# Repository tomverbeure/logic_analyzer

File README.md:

# logic_analyzer

* [Agilent - Probing Solutions for Logic Analyzers](https://xdevs.com/doc/HP_Agilent_Keysight/agilentprobing.pdf)

    * HP/Agilent 01650-61608 - Sixteen-channel probe lead set
        * Also known as E5383A
        * 40 pins: 16 data input, 1 clk input, 2 +5V, 1 DNC, 18 signal ground, 2 +5V ground
        * RC network: 90k ohm/8.2pF
        * Need board connector that is 0.425" tall
    * [3M 8540-4500PL board connector](https://www.digikey.com/en/products/detail/3m/8540-4500PL/1306252)

* [Bidirectional TVS diode for protecting dual-rail power](https://electronics.stackexchange.com/questions/653141/bidirectional-tvs-diode-for-protecting-dual-rail-power)

# Cyclone II LVDS

* [AN 479: Design Guidelines for Implementing LVDS Interfaces in Cyclone Series Devices](https://www.google.com/url?sa=t&rct=j&q=&esrc=s&source=web&cd=&ved=2ahUKEwi85qzynZn9AhXWIkQIHaqIBsoQFnoECDIQAQ&url=https%3A%2F%2Fcdrdv2-public.intel.com%2F653866%2Fan479.pdf)

* [Cyclone® II Device Handbook, Volume 1, Chapter 11: High-Speed Differential Interfaces in Cyclone II Devices](https://www.intel.com/content/www/us/en/content-details/655206/cyclone-ii-device-handbook-volume-1-chapter-11-high-speed-differential-interfaces-in-cyclone-ii-devices.html)

    * RX max 805 Mbps, TX max 640 Mbps.
    * No Vref needed
    * 100 Ohm termination resistor at RX input buffer.
    * (De)serialization is done in core logic.
    * Page 5-63: LVDS receiver timing specification
    * Page 10-27: Pad Placement and DC Guidelines
        * single-ended input no closer than 4 pads away from LVDS I/O
        * single-ended output no closer than 5 pads away from LVDS I/O
        * Maximum 4 155MHz+ LVDS output channels per VCCIO and ground pair
        * Maximum 3 311MHz+ LVDS output channels per VCCIO and ground pair
        * LVDS outputs are 5 or more pads away from LVDS input pad

* [ALTLVDS_TX](https://www.intel.com/content/www/us/en/docs/programmable/683062/17-1/parameter-settings-22420.html)

* [Intel Pin List](https://www.intel.com/content/www/us/en/support/programmable/support-resources/devices/lit-dp.html)

* [LVDS PCB design guidelines](https://madpcb.com/glossary/lvds/)

* [TI - SNx5LVDSxx High-Speed Differential Line Drivers](https://www.ti.com/lit/ds/symlink/sn65lvds31.pdf)

    This datasheet is great for practical layout guidelines. See section 12.

* [TI - LVDS Design Notes](https://www.ti.com/lit/an/slla014a/slla014a.pdf)

    More design guidelines...

* [TI - LVDS Owner’s Manual](https://www.ti.com/lit/ug/snla187/snla187.pdf)

* [LMH7220 - High Speed Comparator with LVDS Outpu](https://www.ti.com/lit/ds/symlink/lmh7322.pdf)

    ~$6 a piece.

* [MAX40025CAWT+T - 280ps High-Speed Comparator, Ultra-Low Dispersion with LVDS Outputs](https://www.mouser.com/datasheet/2/609/MAX40025A_MAX40026-3128703.pdf)

    ~$4.4 a piece for 25+.

# Soldering

* Individual soldering tips on Aliexpress: https://www.aliexpress.us/item/3256802408178790.html
* Drag soldering: https://www.youtube.com/watch?v=5uiroWBkdFY 
* Soldering tips: 
    * Fat/round tip: TS-C4 - reballing
    * Ultra-fin tip: TS-I - fine SMD soldering/fixes
* Mini hotplate
    * https://hackspace.raspberrypi.com/articles/review-miniware-mhp30-mini-hot-plate-preheater
    * 
* BGA Reballing: https://www.youtube.com/watch?v=u8QLlpkyCpc
    * Uses a different jig that doesn't require screws: https://www.aliexpress.us/item/2251832660851140.html
        * magnets
        * rotating knob

* Direct heat reballing (using my jig): https://youtu.be/VTAU647jzzk?t=598
* EP2C35 on AliExpress: https://www.aliexpress.us/item/3256804913471850.html
* 3-in-1 desoldering station: https://www.aliexpress.us/item/3256803049300994.html

# Impedance

* [JLCPCB impedance calculator](https://cart.jlcpcb.com/impedanceCalculation)

    * Impedance + trace space
    * Impedance value: 100 Ohm
    * 4-layer
    * thickness: 1.6mm
    * outer layer (micro-strip)
    * impedance type: differential
    * trace space: 4 mil
    * Result: 
        * JLC3313: 3.49mil  <- chosen
        * JLC7628: 4.96mil
    * Controled impedance PCBs: https://jlcpcb.com/impedance
        * JLC3313
            * Prereg dielectric constant: 4.05
            * Solder mask dielectric constant: 3.8
            * Solder maks thickness: 0.8mil
    
# JLCPCB Plugin

* [Bouni/kicad-jlcpcb-tools](https://github.com/Bouni/kicad-jlcpcb-tools)
* Basic LCSC chips:
    * ESD: SRV05-4-P-T7
    * Voltage inverter: [ICL7660AIBAZA-T](https://www.lcsc.com/product-detail/DC-DC-Converters_RENESAS-ICL7660AIBAZA-T_C7881.html)

# Various

* [Schematic of RISC-V board that uses FT601Q](http://riskfive.com/RiskFive_devel_rev0_board_July_24_2018.pdf)

    * Uses the Xtal that I selected.
    * Uses 25MHz oscillator
    
* ESD info
    * [Littelfuse technical resources](https://www.littelfuse.com/products/tvs-diodes.aspx)
    * USB SS ESD: 
        * [Nexperia PUSB3AB4](https://www.digikey.com/en/products/detail/nexperia-usa-inc/PUSB3AB4Z/6575997)
        * [DigiKey search](https://www.digikey.com/en/products/filter/transient-voltage-suppressors-tvs/tvs-diodes/144?s=N4IgjCBcoKwGxyqAxlAZgQwDYGcCmANCAPZQDaIAnDAAyJFwAsYLlIRYjNNATO%2BGBowAHPxaMA7DX6NhMGM35Mw8Nhx4BmHmvCaN0jvsYaxG2jrAbKPCUubxRHCZVljntN9RMdZNsTBV6cHlNO0DbDiYJGDE4Z0dwCTBhb0T5BLAJYWiZOACNBJ5k7RAAXSIABwAXKBAAZSqAJwBLADsAcxAAXyIJOAhoEFRITFxCEnIQBBpKK34pGg0zMR4aYWEDEFkpCCJ5BUYlFhFY7JL1GE0I8C0aFVNVmmvLfok%2BQ1fN1Z44fX5vuB%2BJzMHjvRLMe5OX6UXaJCRcGJOeE0Q5EUFyJ7-NaXQrYniokBFNarf6MGEpUkwpJlSo1SD1JptTo9RJ-QbDUb4IikSAUWFg1IExFTeb8DIxcogaq1ACSrSqeHaeEa3Q4lGEbHZ6GwXImvJA0lKXWNQA)
    * [Low capacitance 1-channel bidirectional diode: PESD5V0H1BSNYL](https://www.digikey.com/en/products/detail/nexperia-usa-inc/PESD5V0H1BSNYL/12808361)

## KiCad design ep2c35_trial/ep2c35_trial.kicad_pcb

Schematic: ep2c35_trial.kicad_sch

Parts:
C1, C3, C31, C33, C35: 1n; C_0402_1005Metric
C2, C4, C9, C10, C11, C12, C13, C14, C15, C16, C17, C18, C21, C22, C32, C34, C36, C37, C38, C39, C40, C41, C42, C43, C44, C45, C46, C47, C48, C49, C50, C51, C52, C53, C54, C55, C56, C57, C58, C59, C60, C61, C62, C63, C64, C65, C66, C67, C68, C69, C70, C72: 100n; C_0402_1005Metric
C5, C6, C7: 0.1u; C_0402_1005Metric
C8: 4.7u; C_0402_1005Metric
C19, C20: 18p; C_0402_1005Metric
C23, C25: 2u; C_0805_2012Metric
C24, C26: 47u; C_1206_3216Metric
C27, C28, C29, C71, C73: 1u; C_0805_2012Metric
C30: 10u; C_0805_2012Metric
D1, D3, D4, D5, D6, D7, D8: LED; LED_0603_1608Metric
FB1, FB2, FB3: BLM18PG221SN1D; R_0603_1608Metric
J1, J2: Conn_02x21_Odd_Even; PinHeader_2x21_P1.27mm_Horizontal
J3: 3M_8540-4500PL
J4: USB3_B_Micro_Amphenol_GSB343K331HR; AMPHENOL_GSB343K331HR
J5: Conn_02x05_Odd_Even; PinHeader_2x05_P2.54mm_Vertical
J7, J11: Conn_01x03_Pin; PinHeader_1x03_P2.54mm_Vertical
J8, J9: Conn_01x02_Male; PinHeader_1x02_P2.54mm_Vertical
J10: Conn_02x10_Odd_Even; PinHeader_2x10_P1.27mm_Horizontal
R1: 1.6k/1%; R_0402_1005Metric
R2, R3, R4, R5, R6, R7, R10, R31, R32, R33, R34, R35, R36, R37, R38, R39, R40, R41, R42, R43, R44, R45, R46, R47, R48: 10k; R_0402_1005Metric
R8, R68, R69, R71: 5k; R_0402_1005Metric
R9, R72: 3k; R_0402_1005Metric
R11, R12, R13, R14, R15, R16, R17, R18, R19, R20, R21, R22, R23, R24, R25, R26, R27, R28, R29, R30: 100; R_0402_1005Metric
R49, R51, R52, R53, R54, R55, R70: 1k; R_0402_1005Metric
R56, R58, R59, R61, R62, R64, R65, R67: 120; R_0402_1005Metric
R57, R60, R63, R66: 170; R_0402_1005Metric
TP1: TestPoint; TestPoint_Pad_D1.0mm
U1: EP2C35F484; BGA-484_23.0x23.0mm_Layout22x22_P1.0mm
U2: MIC37302; S-PAK-5
U3: FT600Q-B-T; QFN-56-1EP_7x7mm_P0.4mm_FT600Q
U4: W25Q16JVSNIQ; SOIC-8_5.23x5.23mm_P1.27mm
U5: MIC39102; SOICN-8LD-PL-1
U6: MIC49150-1.2; SOICN-8LD-PL-1
U7: SP3003-02UTG; SOT-23-6
U8, U9, U10, U11, U17: SRV05-4; SOT-23-6
U12, U13: LM317_TO-252; TO-252-2
X1: FNETHE025; Oscillator_SMD_IQD_IQXO70-4Pin_7.5x5.0mm
Y1: ABM7-30.000MHZ-D2Y-T; Crystal_SMD_0603-2Pin_6.0x3.5mm_HandSoldering

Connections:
+1V0: C8.2, C16.2, C17.2, C18.2, U3.1 (AVDD), U3.23 (VD10), U3.26 (VD10), U3.31 (DV10), U3.37 (VD10), U3.50 (VD10)
+1V2: C3.1, C4.1, C37.1, C38.1, C39.1, C40.1, C41.1, C42.1, C43.1, C44.1, C45.1, C46.1, C47.1, C48.1, C49.1, D3.2 (A), J8.2, J9.1, U1.E5 (VCCD_PLL3), U1.F17 (VCCD_PLL2), U1.G8 (VCCINT), U1.G12 (VCCINT), U1.H8 (VCCINT), U1.H12 (VCCINT), U1.H13 (VCCINT), U1.J10 (VCCINT), U1.J11 (VCCINT), U1.J12 (VCCINT), U1.J13 (VCCINT), U1.K8 (VCCINT), U1.K9 (VCCINT), U1.K14 (VCCINT), U1.L9 (VCCINT), U1.L14 (VCCINT), U1.L16 (VCCINT), U1.M9 (VCCINT), U1.M14 (VCCINT), U1.N9 (VCCINT), U1.N14 (VCCINT), U1.P10 (VCCINT), U1.P11 (VCCINT), U1.P12 (VCCINT), U1.P13 (VCCINT), U1.P14 (VCCINT), U1.R10 (VCCINT), U1.R12 (VCCINT), U1.T12 (VCCINT), U1.T15 (VCCINT), U1.U6 (VCCD_PLL1), U1.U17 (VCCD_PLL4)
+1V2A: C1.1, C2.1, C30.2, C31.1, C32.1, C33.1, C34.1, C35.1, C36.1, FB3.2, U1.E6 (VCCA_PLL3), U1.F16 (VCCA_PLL2), U1.U7 (VCCA_PLL1), U1.U16 (VCCA_PLL4)
+2V5: C28.2, C50.1, C51.1, C52.1, C53.1, C54.1, C55.1, C56.1, C57.1, C58.1, C59.1, C69.1, D1.2 (A), J11.2, R5.1, R6.1, U1.AA1 (VCCIO1), U1.AA22 (VCCIO6), U1.AB2 (VCCIO8), U1.AB21 (VCCIO7), U1.M3 (VCCIO1), U1.M20 (VCCIO6), U1.P7 (VCCIO1), U1.P16 (VCCIO6), U1.T4 (VCCIO1), U1.T9 (VCCIO8), U1.T14 (VCCIO7), U1.T19 (VCCIO6), U1.V10 (VCCIO8), U1.V13 (VCCIO7), U1.W6 (VCCIO8), U1.W17 (VCCIO7), U1.Y11 (VCCIO8), U1.Y12 (VCCIO7), U6.3 (VIN)
+3.3V: C9.2, C10.2, C11.2, C12.2, C13.2, C14.2, C15.2, C21.1, C22.2, C25.2, C27.2, C60.1, C61.1, C62.1, C63.1, C64.1, C65.1, C66.1, C67.1, C68.1, C70.1, D8.2 (A), J5.4, J7.2, R2.1, R3.2, R4.2, R7.2, U1.A2 (VCCIO3), U1.A21 (VCCIO4), U1.B1 (VCCIO2), U1.B22 (VCCIO5), U1.C6 (VCCIO3), U1.C11 (VCCIO3), U1.C12 (VCCIO4), U1.D17 (VCCIO4), U1.E10 (VCCIO3), U1.E13 (VCCIO4), U1.G9 (VCCIO3), U1.G14 (VCCIO4), U1.G19 (VCCIO5), U1.J7 (VCCIO2), U1.J16 (VCCIO5), U1.L3 (VCCIO2), U1.L20 (VCCIO5), U3.15 (VCC33), U3.19 (VCC33), U3.22 (VDDA), U3.30 (VCC33), U3.38 (VCCIO), U3.44 (VCCIO), U3.52 (VCCIO), U4.8 (VCC), U5.1 (EN), U5.2 (IN), U6.1 (EN), U6.2 (VBIAS), U12.3 (VI), X1.4 (Vdd)
/1V2_LDO: C29.2, J8.1, U6.4 (VOUT)
/1V2_OPT: FB3.1, J9.2
/2V5_ADJ: R10.1, R31.2, U5.4 (ADJ)
/2V5_ADJ_LM: R68.1, R69.2, U12.1 (ADJ)
/2V5_LDO: C26.2, J11.1, R10.2, U5.3 (OUT)
/2V5_LM_LDO: C71.2, J11.3, R68.2, U12.2 (VO)
/3V3_ADJ: R8.1, R9.2, U2.5 (ADJ)
/3V3_ADJ_LM: R71.1, R72.2, U13.1 (ADJ)
/3V3_LDO: C24.2, J7.1, R8.2, U2.4 (VOUT)
/3V3_LM_LDO: C73.2, J7.3, R71.2, U13.2 (VO)
/CLK25: U1.A12 (CLK9/LVDSCLK4p/input), X1.3 (OUT)
/CONF_DONE: R6.2, U1.N18 (CONF_DONE)
/CRC_ERROR: TP1.1, U1.D3 (IO/CRC_ERROR/LVDS49p)
/DIG_CLK: R32.1, U1.L22 (CLK4/LVDSCLK2p/input)
/DIG_D0: R48.1, U1.C21 (IO/LVDS104n)
/DIG_D1: R47.1, U1.C22 (IO/LVDS104p)
/DIG_D2: R46.1, U1.D21 (IO/LVDS108n)
/DIG_D3: R45.1, U1.D22 (IO/LVDS108p)
/DIG_D4: R44.1, U1.E21 (IO/LVDS109n)
/DIG_D5: R43.1, U1.E22 (IO/LVDS109p)
/DIG_D6: R42.1, U1.F21 (IO/LVDS112n)
/DIG_D7: R41.1, U1.F22 (IO/LVDS112p)
/DIG_D8: R40.1, U1.G21 (IO/LVDS114n)
/DIG_D9: R39.1, U1.G22 (IO/LVDS114p)
/DIG_D10: R38.1, U1.H21 (IO/LVDS122n)
/DIG_D11: R37.1, U1.H22 (IO/LVDS122p)
/DIG_D12: R36.1, U1.J21 (IO/LVDS124n)
/DIG_D13: R35.1, U1.J22 (IO/LVDS124p)
/DIG_D14: R34.1, U1.K21 (IO/LVDS125n)
/DIG_D15: R33.1, U1.K22 (IO/LVDS125p)
/FT_BE0: U1.A8 (IO/LVDS62p), U3.2 (BE_0)
/FT_BE1: U1.B8 (IO/LVDS62n), U3.3 (BE_1)
/FT_CLK: U1.B3 (IO/DEV_CLRn/LVDS50n), U3.43 (CLK)
/FT_DATA0: U1.F2 (IO/LVDS36n), U3.33 (DATA_0)
/FT_DATA1: U1.E1 (IO/LVDS37p), U3.34 (DATA_1)
/FT_DATA2: U1.E2 (IO/LVDS37n), U3.35 (DATA_2)
/FT_DATA3: U1.D1 (IO/LVDS40p), U3.36 (DATA_3)
/FT_DATA4: U1.D2 (IO/LVDS40n), U3.39 (DATA_4)
/FT_DATA5: U1.C1 (IO/LVDS47p), U3.40 (DATA_5)
/FT_DATA6: U1.C2 (IO/LVDS47n), U3.41 (DATA_6)
/FT_DATA7: U1.A3 (IO/LVDS50p), U3.42 (DATA_7)
/FT_DATA8: U1.A4 (IO/LVDS51p), U3.45 (DATA_8)
/FT_DATA9: U1.B4 (IO/LVDS51n), U3.46 (DATA_9)
/FT_DATA10: U1.A5 (IO/LVDS52p), U3.47 (DATA_10)
/FT_DATA11: U1.B5 (IO/LVDS52n), U3.48 (DATA_11)
/FT_DATA12: U1.A6 (IO/LVDS53p), U3.53 (DATA_12)
/FT_DATA13: U1.B6 (IO/LVDS53n), U3.54 (DATA_13)
/FT_DATA14: U1.A7 (IO/LVDS61p), U3.55 (DATA_14)
/FT_DATA15: U1.B7 (IO/LVDS61n), U3.56 (DATA_15)
/FT_GPIO0: U1.D9 (IO/LVDS64p), U3.12 (GPIO0)
/FT_GPIO1: U1.C10 (IO/VREFB3N0), U3.13 (GPIO1)
/FT_OE_N: U1.A11 (IO/LVDS73p), U3.9 (OE_N)
/FT_RD_N: U1.B10 (IO/LVDS70n), U3.8 (RD_N)
/FT_RESET_N: U1.B11 (IO/LVDS73n), U3.10 (RESET_N)
/FT_RXF_N: U1.B9 (IO/LVDS67n), U3.5 (RXF_N)
/FT_SIWU_N: R7.1, U3.6 (SIWU_N)
/FT_TXE_N: U1.A9 (IO/LVDS67p), U3.4 (TXE_N)
/FT_WAKEUP_N: U1.C9 (IO/LVDS59p), U3.11 (WAKEUP_N)
/FT_WR_N: U1.A10 (IO/LVDS70p), U3.7 (WR_N)
/LED0: D4.2 (A), U1.G1 (IO/LVDS31p)
/LED1: D5.2 (A), U1.G2 (IO/LVDS31n)
/LED2: D6.2 (A), U1.H1 (IO/LVDS29p)
/LED3: D7.2 (A), U1.H2 (IO/LVDS29n)
/LVDS2: U1.W3 (IO/LVDS2p), U1.W4 (IO/LVDS2n)
/LVDS7: U1.T5 (IO/LVDS7p), U1.T6 (IO/LVDS7n)
/LVDS10: U1.R5 (IO/LVDS10p), U1.R6 (IO/LVDS10n)
/LVDS12: U1.P4 (IO/LVDS12p), U1.R4 (IO/LVDS12n)
/LVDS17: U1.P5 (IO/LVDS17p), U1.P6 (IO/LVDS17n)
/LVDS18: U1.R7 (IO/LVDS18n), U1.R8 (IO/LVDS18p)
/LVDS20: U1.N3 (IO/LVDS20p), U1.N4 (IO/LVDS20n)
/LVDS22: U1.N5 (IO/LVDS22n), U1.N6 (IO/LVDS22p)
/LVDS23: U1.M7 (IO/LVDS23n), U1.M8 (IO/LVDS23p)
/LVDS26: U1.M5 (IO/LVDS26p), U1.M6 (IO/LVDS26n)
/LVDS48: U1.E3 (IO/LVDS48p), U1.E4 (IO/LVDS48n)
/LVDS76: U1.A14 (IO/LVDS76p), U1.B14 (IO/LVDS76n)
/LVDS96: U1.A18 (IO/LVDS96p), U1.B18 (IO/LVDS96n)
/LVDS97: U1.A19 (IO/LVDS97p), U1.B19 (IO/LVDS97n)
/LVDS98: U1.A20 (IO/LVDS98p), U1.B20 (IO/LVDS98n)
/LVDS100: U1.D19 (IO/LVDS100n), U1.D20 (IO/LVDS100p)
/LVDS101: U1.C19 (IO/LVDS101n), U1.C20 (IO/LVDS101p)
/LVDS105: U1.E20 (IO/LVDS105n), U1.F20 (IO/LVDS105p)
/LVDS111: U1.H17 (IO/LVDS111p), U1.H18 (IO/LVDS111n)
/LVDS117: U1.J18 (IO/LVDS117p), U1.J19 (IO/LVDS117n)
/LVDS120: U1.H19 (IO/LVDS120p), U1.J20 (IO/LVDS120n)
/LVDS130: U1.M15 (IO/LVDS130p), U1.M16 (IO/LVDS130n)
/LVDS132: U1.N15 (IO/LVDS132p), U1.P15 (IO/LVDS132n)
/LVDS152: U1.AA19 (IO/LVDS152n), U1.AB19 (IO/LVDS152p)
/LVDS168: U1.AA16 (IO/LVDS168n), U1.AB16 (IO/LVDS168p)
/LVDS169: U1.AA15 (IO/LVDS169n), U1.AB15 (IO/LVDS169p)
/LVDS170: U1.AA14 (IO/LVDS170n), U1.AB14 (IO/LVDS170p)
/LVDS174: U1.AA13 (IO/LVDS174n), U1.AB13 (IO/LVDS174p)
/LVDS176: U1.AA12 (IO/LVDS176n), U1.AB12 (IO/LVDS176p)
/LVDS177: U1.AA11 (IO/LVDS177n), U1.AB11 (IO/LVDS177p)
/LVDS197: U1.AA5 (IO/LVDS197n), U1.AB5 (IO/LVDS197p)
/LVDS198: U1.Y5 (IO/LVDS198p), U1.Y6 (IO/LVDS198n)
/LVDS_RX_CLK0_N: J1.39, R30.1, U1.M2 (CLK3/LVDSCLK1n/input)
/LVDS_RX_CLK0_P: J1.41, R30.2, U1.M1 (CLK2/LVDSCLK1p/input)
/LVDS_RX_CLK1_N: J2.39, R20.1, U1.M21 (CLK7/LVDSCLK3n/input)
/LVDS_RX_CLK1_P: J2.41, R20.2, U1.M22 (CLK6/LVDSCLK3p/input)
/LVDS_RX_DATA0_0_N: J1.35, R28.1, U1.N2 (IO/LVDS25n)
/LVDS_RX_DATA0_0_P: J1.37, R28.2, U1.N1 (IO/LVDS25p)
/LVDS_RX_DATA0_1_N: J1.31, R27.1, U1.P2 (IO/LVDS24n)
/LVDS_RX_DATA0_1_P: J1.33, R27.2, U1.P1 (IO/LVDS24p)
/LVDS_RX_DATA0_2_N: J1.27, R26.1, U1.R2 (IO/LVDS16n)
/LVDS_RX_DATA0_2_P: J1.29, R26.2, U1.R1 (IO/LVDS16p)
/LVDS_RX_DATA0_3_N: J1.23, R25.1, U1.T2 (IO/LVDS13n)
/LVDS_RX_DATA0_3_P: J1.25, R25.2, U1.T1 (IO/LVDS13p)
/LVDS_RX_DATA0_4_N: J1.19, R24.1, U1.U2 (IO/LVDS11n)
/LVDS_RX_DATA0_4_P: J1.21, R24.2, U1.U1 (IO/LVDS11p)
/LVDS_RX_DATA0_5_N: J1.15, R23.1, U1.V2 (IO/LVDS8n)
/LVDS_RX_DATA0_5_P: J1.17, R23.2, U1.V1 (IO/LVDS8p)
/LVDS_RX_DATA0_6_N: J1.11, R22.1, U1.W2 (IO/LVDS6n)
/LVDS_RX_DATA0_6_P: J1.13, R22.2, U1.W1 (IO/LVDS6p)
/LVDS_RX_DATA0_7_N: J1.7, R21.1, U1.Y2 (IO/LVDS5n)
/LVDS_RX_DATA0_7_P: J1.9, R21.2, U1.Y1 (IO/LVDS5p)
/LVDS_RX_DATA1_0_N: J2.31, R18.1, U1.Y21 (IO/LVDS141n)
/LVDS_RX_DATA1_0_P: J2.33, R18.2, U1.Y22 (IO/LVDS141p)
/LVDS_RX_DATA1_1_N: J2.27, R17.1, U1.W21 (IO/LVDS145n)
/LVDS_RX_DATA1_1_P: J2.29, R17.2, U1.W22 (IO/LVDS145p)
/LVDS_RX_DATA1_2_N: J2.23, R16.1, U1.V21 (IO/LVDS140n)
/LVDS_RX_DATA1_2_P: J2.25, R16.2, U1.V22 (IO/LVDS140p)
/LVDS_RX_DATA1_3_N: J2.19, R15.1, U1.U21 (IO/LVDS139n)
/LVDS_RX_DATA1_3_P: J2.21, R15.2, U1.U22 (IO/LVDS139p)
/LVDS_RX_DATA1_4_N: J2.15, R14.1, U1.T21 (IO/LVDS135n)
/LVDS_RX_DATA1_4_P: J2.17, R14.2, U1.T22 (IO/LVDS135p)
/LVDS_RX_DATA1_5_N: J2.11, R13.1, U1.R21 (IO/LVDS134n)
/LVDS_RX_DATA1_5_P: J2.13, R13.2, U1.R22 (IO/LVDS134p)
/LVDS_RX_DATA1_6_N: J2.7, R12.1, U1.P21 (IO/LVDS129n)
/LVDS_RX_DATA1_6_P: J2.9, R12.2, U1.P22 (IO/LVDS129p)
/LVDS_RX_DATA1_7_N: J2.3, R11.1, U1.N21 (IO/LVDS128n)
/LVDS_RX_DATA1_7_P: J2.5, R11.2, U1.N22 (IO/LVDS128p)
/LVDS_RX_FCLK0_N: J1.3, R29.1, U1.Y4 (IO/LVDS0n)
/LVDS_RX_FCLK0_P: J1.5, R29.2, U1.Y3 (IO/LVDS0p)
/LVDS_RX_FCLK1_N: J2.35, R19.1, U1.Y19 (IO/LVDS149n)
/LVDS_RX_FCLK1_P: J2.37, R19.2, U1.Y20 (IO/LVDS149p)
/LVDS_TX_DATA0_N: J10.5, R56.1, R57.2
/LVDS_TX_DATA0_P: J10.3, R57.1, R58.1
/LVDS_TX_DATA0_RAW_N: R56.2, U1.AA10 (IO/LVDS178n)
/LVDS_TX_DATA0_RAW_P: R58.2, U1.AB10 (IO/LVDS178p)
/LVDS_TX_DATA1_N: J10.9, R59.1, R60.2
/LVDS_TX_DATA1_P: J10.7, R60.1, R61.1
/LVDS_TX_DATA1_RAW_N: R59.2, U1.AA9 (IO/LVDS181n)
/LVDS_TX_DATA1_RAW_P: R61.2, U1.AB9 (IO/LVDS181p)
/LVDS_TX_DATA2_N: J10.13, R62.1, R63.2
/LVDS_TX_DATA2_P: J10.11, R63.1, R64.1
/LVDS_TX_DATA2_RAW_N: R62.2, U1.AA8 (IO/LVDS183n)
/LVDS_TX_DATA2_RAW_P: R64.2, U1.AB8 (IO/LVDS183p)
/LVDS_TX_DATA3_N: J10.17, R65.1, R66.2
/LVDS_TX_DATA3_P: J10.15, R66.1, R67.1
/LVDS_TX_DATA3_RAW_N: R65.2, U1.AA7 (IO/LVDS189n)
/LVDS_TX_DATA3_RAW_P: R67.2, U1.AB7 (IO/LVDS189p)
/POD_CLK: J3.3 (CLOCK), R32.2, U11.1 (IO1)
/POD_D0: J3.37 (D0), R48.2, U17.1 (IO1)
/POD_D1: J3.35 (D1), R47.2, U17.3 (IO2)
/POD_D2: J3.33 (D2), R46.2, U17.4 (IO3)
/POD_D3: J3.31 (D3), R45.2, U17.6 (IO4)
/POD_D4: J3.29 (D4), R44.2, U8.1 (IO1)
/POD_D5: J3.27 (D5), R43.2, U8.3 (IO2)
/POD_D6: J3.25 (D6), R42.2, U8.4 (IO3)
/POD_D7: J3.23 (D7), R41.2, U8.6 (IO4)
/POD_D8: J3.21 (D8), R40.2, U9.1 (IO1)
/POD_D9: J3.19 (D9), R39.2, U9.3 (IO2)
/POD_D10: J3.17 (D10), R38.2, U9.4 (IO3)
/POD_D11: J3.15 (D11), R37.2, U9.6 (IO4)
/POD_D12: J3.13 (D12), R36.2, U10.1 (IO1)
/POD_D13: J3.11 (D13), R35.2, U10.3 (IO2)
/POD_D14: J3.9 (D14), R34.2, U10.4 (IO3)
/POD_D15: J3.7 (D15), R33.2, U10.6 (IO4)
/SPI_ADS: U1.C4 (IO/ASDO), U4.5 (DI(IO0))
/SPI_DATA0: U1.K4 (DATA0), U4.2 (DO(IO1))
/SPI_DCLK: U1.L6 (DCLK), U4.6 (CLK)
/SPI_nCS: U1.C3 (IO/nCSO), U4.1 (~CS)
/SPI_nRESET: R4.1, U4.7 (IO3)
/SPI_nWP: R3.1, U4.3 (IO2)
/TCK: J5.1, U1.K2 (TCK)
/TDI: J5.9, U1.K5 (TDI)
/TDO: J5.3, U1.L5 (TDO)
/TMS: J5.5, U1.K6 (TMS)
/USB_D_N: J4.2 (D-), U3.20 (DM), U7.1, U7.6
/USB_D_P: J4.3 (D+), U3.18 (DP), U7.2, U7.5
/USB_RREF: R1.1, U3.21 (RREF)
/USB_SHIELD: FB2.1, J4.S1 (SHIELD), J4.S2 (SHIELD)
/USB_SSRX_N: J4.9 (SSRX-), U3.27 (RIDN)
/USB_SSRX_P: J4.10 (SSRX+), U3.28 (RIDP)
/USB_SSTX_N: C6.2, U3.24 (TODN)
/USB_SSTX_P: C7.2, U3.25 (TODP)
/USB_SSTX_RAW_N: C6.1, J4.6 (SSTX-)
/USB_SSTX_RAW_P: C7.1, J4.7 (SSTX+)
/VBUS: C23.2, C72.1, FB1.1, J3.1 (+5V), J3.39 (+5V), U2.1 (EN), U2.2 (VIN), U3.29 (VBUS), U13.3 (VI)
/VBUS_RAW: C5.1, FB1.2, J4.1 (VBUS)
/nSTATUS: R5.2, U1.N20 (nSTATUS)
GNDD: C1.2, C2.2, C3.2, C4.2, C5.2, C8.1, C9.1, C10.1, C11.1, C12.1, C13.1, C14.1, C15.1, C16.1, C17.1, C18.1, C19.1, C20.1, C21.2, C22.1, C23.1, C24.1, C25.1, C26.1, C27.1, C28.1, C29.1, C30.1, C31.2, C32.2, C33.2, C34.2, C35.2, C36.2, C37.2, C38.2, C39.2, C40.2, C41.2, C42.2, C43.2, C44.2, C45.2, C46.2, C47.2, C48.2, C49.2, C50.2, C51.2, C52.2, C53.2, C54.2, C55.2, C56.2, C57.2, C58.2, C59.2, C60.2, C61.2, C62.2, C63.2, C64.2, C65.2, C66.2, C67.2, C68.2, C69.2, C70.2, C71.1, C72.2, C73.1, FB2.2, J1.1, J1.2, J1.4, J1.6, J1.8, J1.10, J1.12, J1.14, J1.16, J1.18, J1.20, J1.22, J1.24, J1.26, J1.28, J1.30, J1.32, J1.34, J1.36, J1.38, J1.40, J1.42, J2.1, J2.2, J2.4, J2.6, J2.8, J2.10, J2.12, J2.14, J2.16, J2.18, J2.20, J2.22, J2.24, J2.26, J2.28, J2.30, J2.32, J2.34, J2.36, J2.38, J2.40, J2.42, J3.2 (PGND), J3.4 (GND), J3.6 (GND), J3.8 (GND), J3.10 (GND), J3.12 (GND), J3.14 (GND), J3.16 (GND), J3.18 (GND), J3.20 (GND), J3.22 (GND), J3.24 (GND), J3.26 (GND), J3.28 (GND), J3.30 (GND), J3.32 (GND), J3.34 (GND), J3.36 (GND), J3.38 (GND), J3.40 (PGND), J4.5 (GND), J4.8 (DRAIN), J5.2, J5.10, J10.1, J10.2, J10.4, J10.6, J10.8, J10.10, J10.12, J10.14, J10.16, J10.18, J10.19, J10.20, R1.2, R9.1, R31.1, R49.1, R51.1, R52.1, R53.1, R54.1, R55.1, R69.1, R70.1, R72.1, U1.A1 (GND), U1.A22 (GND), U1.AA2 (GND), U1.AA21 (GND), U1.AB1 (GND), U1.AB22 (GND), U1.B2 (GND), U1.B21 (GND), U1.C5 (GND), U1.C8 (GND), U1.C15 (GND), U1.D10 (GND), U1.D13 (GND), U1.D18 (GND), U1.E16 (GNDA_PLL2), U1.E17 (GND_PLL2), U1.F5 (GND_PLL3), U1.F6 (GND_PLL3), U1.F7 (GNDA_PLL3), U1.F18 (GND_PLL2), U1.F19 (GND), U1.G4 (GND), U1.G10 (GND), U1.G13 (GND), U1.G15 (GND), U1.H9 (GND), U1.H10 (GND), U1.H20 (GND), U1.J8 (GND), U1.J9 (GND), U1.K1 (nCE), U1.K3 (GND), U1.K7 (GND), U1.K10 (GND), U1.K11 (GND), U1.K12 (GND), U1.K13 (GND), U1.K15 (GND), U1.K16 (GND), U1.K19 (GND), U1.L10 (GND), U1.L11 (GND), U1.L12 (GND), U1.L13 (GND), U1.L15 (GND), U1.M4 (GND), U1.M10 (GND), U1.M11 (GND), U1.M12 (GND), U1.M13 (GND), U1.M17 (MSEL0), U1.N7 (GND), U1.N8 (GND), U1.N10 (GND), U1.N11 (GND), U1.N12 (GND), U1.N13 (GND), U1.N16 (GND), U1.N17 (MSEL1), U1.N19 (GND), U1.P8 (GND), U1.P9 (GND), U1.R3 (GND), U1.R9 (GND), U1.R13 (GND), U1.T10 (GND), U1.T13 (GND), U1.T17 (GND_PLL4), U1.T20 (GND), U1.U5 (GND_PLL1), U1.V3 (GND), U1.V5 (GND_PLL1), U1.V6 (GND), U1.V7 (GNDA_PLL1), U1.V16 (GNDA_PLL4), U1.V17 (GND), U1.V18 (GND_PLL4), U1.W10 (GND), U1.W13 (GND), U1.W19 (GND), U1.Y8 (GND), U1.Y15 (GND), U2.3 (GND), U3.32 (GND), U3.49 (GND), U3.51 (GND), U3.57 (GND), U4.4 (GND), U5.5 (GND), U5.6 (GND), U5.7 (GND), U5.8 (GND), U6.5 (GND), U6.6 (GND), U6.7 (GND), U6.8 (GND), U7.3, U7.4, U8.2 (VN), U9.2 (VN), U10.2 (VN), U11.2 (VN), U11.3 (IO2), U11.4 (IO3), U11.6 (IO4), U17.2 (VN), X1.2 (GND)
unnamed: D1.1 (K), R49.2
unnamed: D3.1 (K), R51.2
unnamed: D4.1 (K), R52.2
unnamed: D5.1 (K), R53.2
unnamed: D6.1 (K), R54.2
unnamed: D7.1 (K), R55.2
unnamed: D8.1 (K), R70.2
unnamed: U1.V4 (IO/PLL1_OUTn), U1.W5 (IO)
unnamed: U1.U3 (IO/VREFB1N1), U1.U4 (IO/PLL1_OUTp)
unnamed: U1.P3 (IO/VREFB1N0), U1.T3 (IO)
unnamed: R2.2, U1.L4 (nCONFIG)
unnamed: C20.2, U3.16 (XI), Y1.2
unnamed: C19.2, U3.17 (XO), Y1.1

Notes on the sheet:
Vout=1.25(1+R1/R2) + Iadj*R2 -> 2.5V
Vout=1.24(1+R1/R2) -> 3.3V
Vout=1.24(1+R1/R2) -> 2.48V

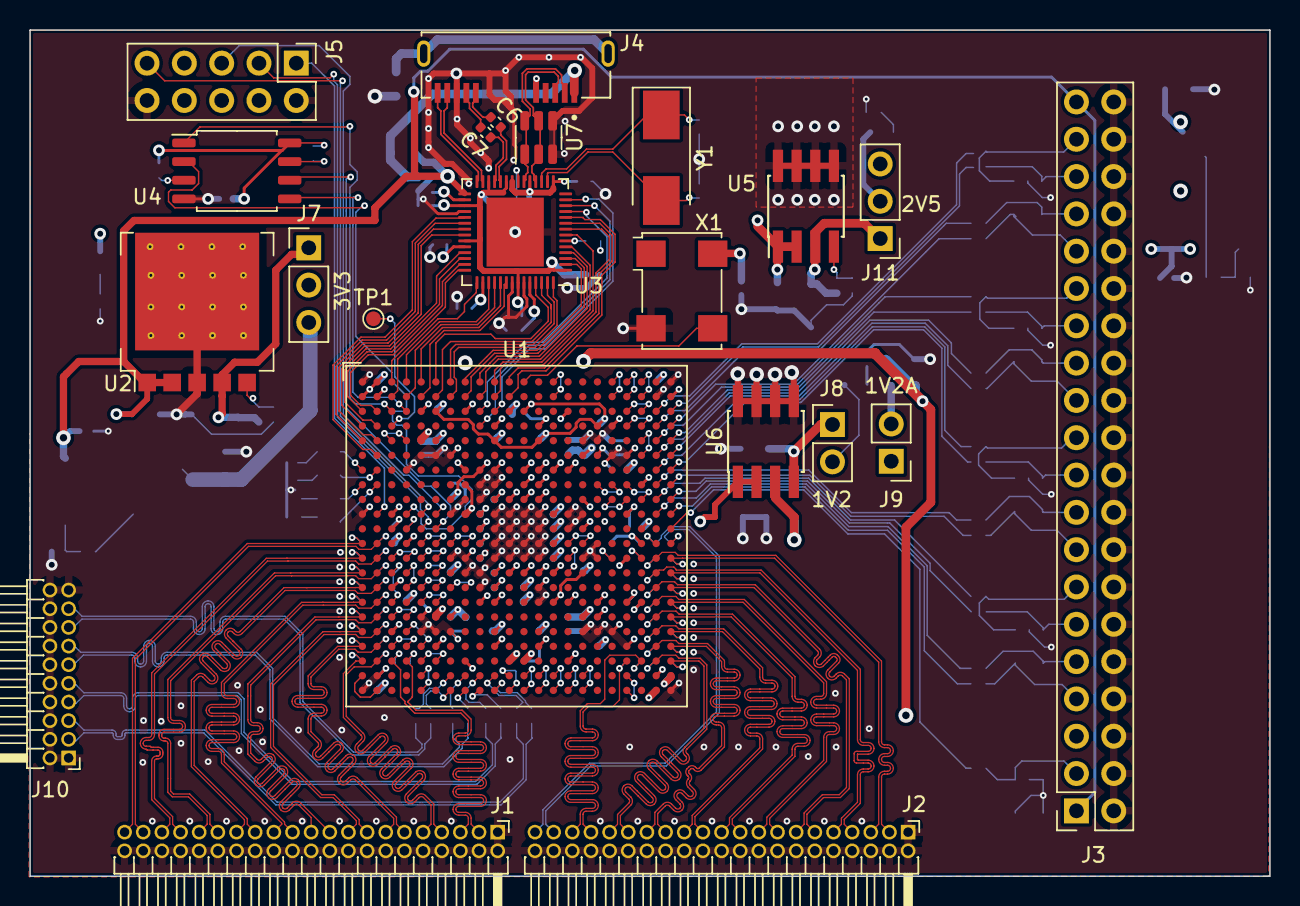
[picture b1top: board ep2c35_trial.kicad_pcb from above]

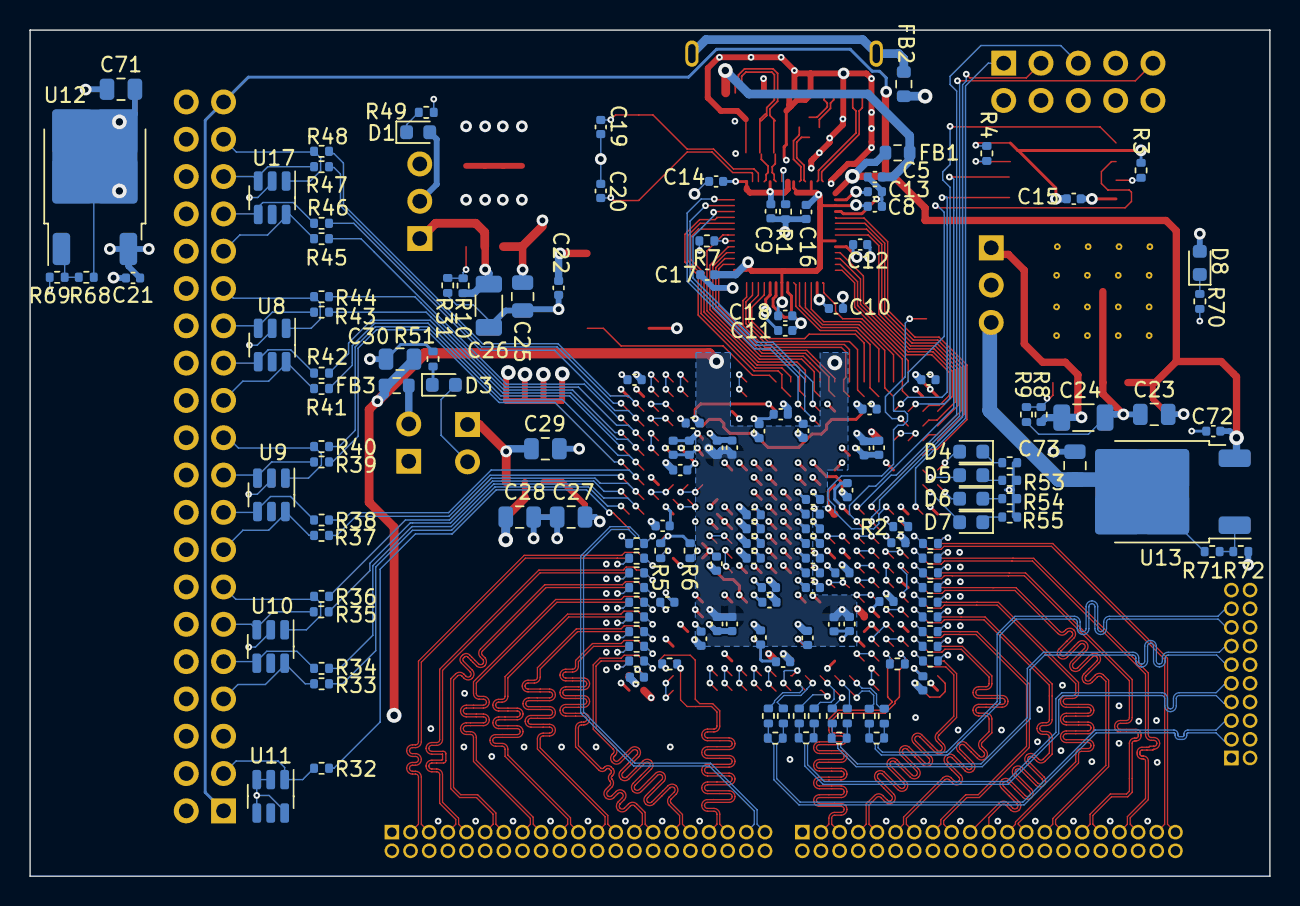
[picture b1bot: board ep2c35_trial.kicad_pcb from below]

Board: 4 copper layers, 84.4 x 57.6 mm, 181 parts (159 on the bottom side), 210 nets.

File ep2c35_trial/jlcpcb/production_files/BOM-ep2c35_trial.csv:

Comment,Designator,Footprint,LCSC
1n,"C1,C3,C31,C33,C35",C_0402_1005Metric,C1523
100n,"C10,C11,C12,C13,C14,C15,C16,C17,C18,C2,C22,C32,C34,C36,C37,C38,C39,C4,C40,C41,C42,C43,C44,C45,C46,C47,C48,C49,C5,C50,C51,C52,C53,C54,C55,C56,C57,C58,C59,C6,C60,C61,C62,C63,C64,C65,C66,C67,C68,C69,C7,C70,C9",C_0402_1005Metric,C1525
18p,"C19,C20",C_0402_1005Metric,C1549
10u,C30,C_0805_2012Metric,C15850
4.7u,"C21,C8",C_0402_1005Metric,C23733
10k,"R10,R11,R12,R13,R14,R15,R16,R17,R18,R19,R2,R20,R21,R22,R23,R24,R25,R26,R27,R28,R29,R3,R30,R31,R32,R33,R34,R35,R36,R37,R38,R39,R4,R40,R41,R42,R43,R44,R45,R46,R47,R48,R5,R6,R7,R8,R9",R_0402_1005Metric,C25744
1u,"C27,C28,C29",C_0805_2012Metric,C28323
2u,"C23,C25",C_0805_2012Metric,C45783
BLM18PG221SN1D,"FB1,FB2,FB3",R_0603_1608Metric,C80165
47u,"C24,C26",C_1206_3216Metric,C96123
Conn_01x02_Male,J6,PinHeader_1x02_P2.54mm_Vertical,
Conn_02x21_Odd_Even,J2,PinHeader_2x21_P1.27mm_Horizontal,
Conn_01x02_Male,J9,PinHeader_1x02_P2.54mm_Vertical,
W25Q16JVSNIQ,U4,SOIC-8_5.23x5.23mm_P1.27mm,
1.6k/1%,R1,R_0402_1005Metric,
Conn_02x05_Odd_Even,J5,PinHeader_2x05_P2.54mm_Vertical,
Conn_02x21_Odd_Even,J1,PinHeader_2x21_P1.27mm_Horizontal,
Conn_01x02_Male,J8,PinHeader_1x02_P2.54mm_Vertical,
USB3_B_Micro_Amphenol_GSB343K331HR,J4,AMPHENOL_GSB343K331HR,
Conn_01x02_Male,J7,PinHeader_1x02_P2.54mm_Vertical,

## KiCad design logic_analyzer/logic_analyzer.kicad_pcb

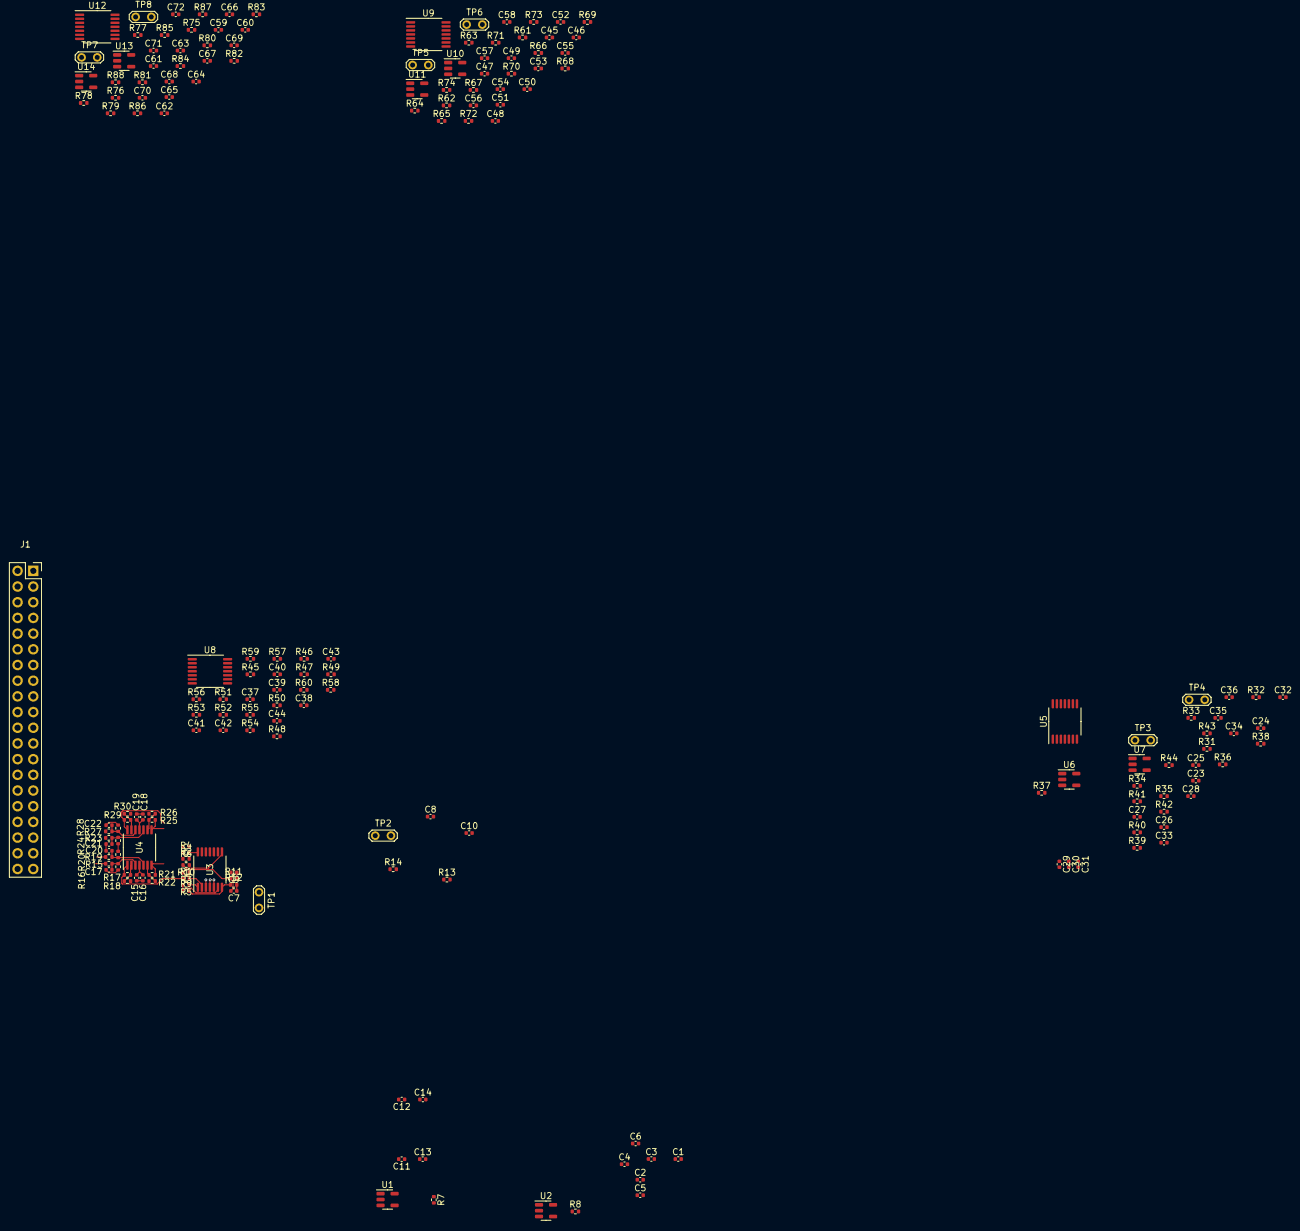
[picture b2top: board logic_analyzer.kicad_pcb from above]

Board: 4 copper layers, 183 parts (0 on the bottom side), 93 nets.

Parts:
C1, C2, C29, C34, C51, C56, C65, C70: 100p; C_0402_1005Metric
C3, C4, C30, C35, C52, C57, C66, C71: 10n; C_0402_1005Metric
C5, C6, C31, C36, C53, C58, C67, C72: 1u; C_0402_1005Metric
C7, C8, C9, C10, C25, C26, C32, C33, C47, C48, C54, C55, C61, C62, C68, C69: 30p; C_0402_1005Metric
C11, C12, C15, C18, C23, C27, C37, C40, C45, C49, C59, C63: 100n; C_0402_1005Metric
C13, C14, C16, C19, C24, C28, C38, C41, C46, C50, C60, C64: 10u; C_0402_1005Metric
C17, C20, C21, C22, C39, C42, C43, C44: 70p; C_0402_1005Metric
J1: 3M_8540-4500PL
R1, R2, R34, R41, R64, R71, R78, R85: 1.5k; R_0402_1005Metric
R3, R4, R5, R6, R9, R10, R17, R21, R25, R29, R32, R33, R35, R39, R40, R42, R47, R51, R55, R59, R62, R63, R65, R69, R70, R72, R76, R77, R79, R83, R84, R86: 1k; R_0402_1005Metric
R7, R8, R37, R44, R67, R74, R81, R88: 20; R_0402_1005Metric
R11, R13, R31, R38, R61, R68, R75, R82: 100; R_0402_1005Metric
R12, R14, R36, R43, R66, R73, R80, R87: 150; R_0402_1005Metric
R15, R19, R23, R27, R45, R49, R53, R57: 250; R_0402_1005Metric
R16, R20, R24, R28, R46, R50, R54, R58: 10k; R_0402_1005Metric
R18, R22, R26, R30, R48, R52, R56, R60: 3k; R_0402_1005Metric
TP1, TP2, TP3, TP4, TP5, TP6, TP7, TP8: TestPoint_2Pole; TestPoint_2Pads_Pitch2.54mm_Drill0.8mm
U1, U2, U6, U7, U10, U11, U13, U14: TLV3601; SOT-23-5
U3, U4, U5, U8, U9, U12: ADA4891-4; TSSOP-14_4.4x5mm_P0.65mm

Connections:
+3.3V: C1.1, C2.1, C3.1, C4.1, C5.1, C6.1, C29.1, C30.1, C31.1, C34.1, C35.1, C36.1, C51.1, C52.1, C53.1, C56.1, C57.1, C58.1, C65.1, C66.1, C67.1, C70.1, C71.1, C72.1, U1.5 (V+), U2.5 (V+), U6.5 (V+), U7.5 (V+), U10.5 (V+), U11.5 (V+), U13.5 (V+), U14.5 (V+)
+5V: J1.1 (+5V), J1.39 (+5V)
+5VA: C11.1, C13.1, C15.1, C16.1, C23.1, C24.1, C37.1, C38.1, C45.1, C46.1, C59.1, C60.1, U3.4 (V+), U4.4 (V+), U5.4 (V+), U8.4 (V+), U9.4 (V+), U12.4 (V+)
-5VA: C12.1, C14.1, C18.1, C19.1, C27.1, C28.1, C40.1, C41.1, C49.1, C50.1, C63.1, C64.1, U3.11 (V-), U4.11 (V-), U5.11 (V-), U8.11 (V-), U9.11 (V-), U12.11 (V-)
/BUF_OUT0: R1.1, R17.2, U1.3 (+), U4.1
/BUF_OUT1: R2.1, R21.2, U2.3 (+), U4.7
/BUF_OUT2: R25.2, R34.1, U4.8, U6.3 (+)
/BUF_OUT3: R29.2, R41.1, U4.14, U7.3 (+)
/BUF_OUT4: R47.2, R64.1, U8.1, U10.3 (+)
/BUF_OUT5: R51.2, R71.1, U8.7, U11.3 (+)
/BUF_OUT6: R55.2, R78.1, U8.8, U13.3 (+)
/BUF_OUT7: R59.2, R85.1, U8.14, U14.3 (+)
/Input Section1/ADC_IN+: C25.1, C32.1, R31.2, R38.2, TP3.2, TP4.2
/Input Section1/ADC_IN-: C26.1, C33.1, R36.2, R43.2, TP3.1, TP4.1
/Input Section1/OA1_out: R31.1, R32.2, R35.1, U5.1
/Input Section1/OA2_out: R33.2, R36.1, U5.7
/Input Section1/OA3_out: R38.1, R39.2, R42.1, U5.14
/Input Section1/OA4_out: R40.2, R43.1, U5.8
/Input Section1/Vcom: U5.5 (+), U5.10 (+)
/Input Section2/ADC_IN+: C47.1, C54.1, R61.2, R68.2, TP5.2, TP6.2
/Input Section2/ADC_IN-: C48.1, C55.1, R66.2, R73.2, TP5.1, TP6.1
/Input Section2/OA1_out: R61.1, R62.2, R65.1, U9.1
/Input Section2/OA2_out: R63.2, R66.1, U9.7
/Input Section2/OA3_out: R68.1, R69.2, R72.1, U9.14
/Input Section2/OA4_out: R70.2, R73.1, U9.8
/Input Section2/Vcom: U9.5 (+), U9.10 (+)
/Input Section3/ADC_IN+: C61.1, C68.1, R75.2, R82.2, TP7.2, TP8.2
/Input Section3/ADC_IN-: C62.1, C69.1, R80.2, R87.2, TP7.1, TP8.1
/Input Section3/OA1_out: R75.1, R76.2, R79.1, U12.1
/Input Section3/OA2_out: R77.2, R80.1, U12.7
/Input Section3/OA3_out: R82.1, R83.2, R86.1, U12.14
/Input Section3/OA4_out: R84.2, R87.1, U12.8
/Input Section3/Vcom: U12.5 (+), U12.10 (+)
/Input Section/ADC_IN+: C9.1, C10.1, R11.2, R13.2, TP1.2, TP2.2
/Input Section/ADC_IN-: C7.1, C8.1, R12.2, R14.2, TP1.1, TP2.1
/Input Section/OA1_out: R3.2, R5.1, R11.1, U3.1
/Input Section/OA2_out: R9.2, R12.1, U3.7
/Input Section/OA3_out: R4.2, R6.1, R13.1, U3.14
/Input Section/OA4_out: R10.2, R14.1, U3.8
/Input Section/Vcom: U3.5 (+), U3.10 (+)
/Input Section/Voffset2: U3.3 (+), U3.12 (+), U5.3 (+), U5.12 (+), U9.3 (+), U9.12 (+), U12.3 (+), U12.12 (+)
/Input Section/Vthresh: U1.4 (-), U2.4 (-), U6.4 (-), U7.4 (-), U10.4 (-), U11.4 (-), U13.4 (-), U14.4 (-)
/POD_D0: J1.37 (D0), R15.1
/POD_D1: J1.35 (D1), R19.1
/POD_D2: J1.33 (D2), R23.1
/POD_D3: J1.31 (D3), R27.1
/POD_D4: J1.29 (D4), R45.1
/POD_D5: J1.27 (D5), R49.1
/POD_D6: J1.25 (D6), R53.1
/POD_D7: J1.23 (D7), R57.1
/Voff_buf: R18.1, R22.1, R26.1, R30.1, R48.1, R52.1, R56.1, R60.1
/pod_buf4/BUF_IN0: C17.1, R15.2, R16.2, U4.3 (+)
/pod_buf4/BUF_IN1: C20.1, R19.2, R20.2, U4.5 (+)
/pod_buf4/BUF_IN2: C21.1, R23.2, R24.2, U4.10 (+)
/pod_buf4/BUF_IN3: C22.1, R27.2, R28.2, U4.12 (+)
/pod_buf5/BUF_IN0: C39.1, R45.2, R46.2, U8.3 (+)
/pod_buf5/BUF_IN1: C42.1, R49.2, R50.2, U8.5 (+)
/pod_buf5/BUF_IN2: C43.1, R53.2, R54.2, U8.10 (+)
/pod_buf5/BUF_IN3: C44.1, R57.2, R58.2, U8.12 (+)
GNDA: C7.2, C8.2, C9.2, C10.2, C11.2, C12.2, C13.2, C14.2, C15.2, C16.2, C17.2, C18.2, C19.2, C20.2, C21.2, C22.2, C23.2, C24.2, C25.2, C26.2, C27.2, C28.2, C32.2, C33.2, C37.2, C38.2, C39.2, C40.2, C41.2, C42.2, C43.2, C44.2, C45.2, C46.2, C47.2, C48.2, C49.2, C50.2, C54.2, C55.2, C59.2, C60.2, C61.2, C62.2, C63.2, C64.2, C68.2, C69.2, J1.4 (GND), J1.6 (GND), J1.8 (GND), J1.10 (GND), J1.12 (GND), J1.14 (GND), J1.16 (GND), J1.18 (GND), J1.20 (GND), J1.22 (GND), J1.24 (GND), J1.26 (GND), J1.28 (GND), J1.30 (GND), J1.32 (GND), J1.34 (GND), J1.36 (GND), J1.38 (GND), R16.1, R20.1, R24.1, R28.1, R46.1, R50.1, R54.1, R58.1
GNDD: C1.2, C2.2, C3.2, C4.2, C5.2, C6.2, C29.2, C30.2, C31.2, C34.2, C35.2, C36.2, C51.2, C52.2, C53.2, C56.2, C57.2, C58.2, C65.2, C66.2, C67.2, C70.2, C71.2, C72.2, J1.2 (PGND), J1.40 (PGND), U1.2 (V-), U2.2 (V-), U6.2 (V-), U7.2 (V-), U10.2 (V-), U11.2 (V-), U13.2 (V-), U14.2 (V-)
unnamed: R7.1, U1.1
unnamed: R8.1, U2.1
unnamed: R37.1, U6.1
unnamed: R44.1, U7.1
unnamed: R67.1, U10.1
unnamed: R74.1, U11.1
unnamed: R81.1, U13.1
unnamed: R88.1, U14.1
unnamed: R1.2, R3.1, U3.2 (-)
unnamed: R5.2, R9.1, U3.6 (-)
unnamed: R6.2, R10.1, U3.9 (-)
unnamed: R2.2, R4.1, U3.13 (-)
unnamed: R17.1, R18.2, U4.2 (-)
unnamed: R21.1, R22.2, U4.6 (-)
unnamed: R25.1, R26.2, U4.9 (-)
unnamed: R29.1, R30.2, U4.13 (-)
unnamed: R32.1, R34.2, U5.2 (-)
unnamed: R33.1, R35.2, U5.6 (-)
unnamed: R40.1, R42.2, U5.9 (-)
unnamed: R39.1, R41.2, U5.13 (-)
unnamed: R47.1, R48.2, U8.2 (-)
unnamed: R51.1, R52.2, U8.6 (-)
unnamed: R55.1, R56.2, U8.9 (-)
unnamed: R59.1, R60.2, U8.13 (-)
unnamed: R62.1, R64.2, U9.2 (-)
unnamed: R63.1, R65.2, U9.6 (-)
unnamed: R70.1, R72.2, U9.9 (-)
unnamed: R69.1, R71.2, U9.13 (-)
unnamed: R76.1, R78.2, U12.2 (-)
unnamed: R77.1, R79.2, U12.6 (-)
unnamed: R84.1, R86.2, U12.9 (-)
unnamed: R83.1, R85.2, U12.13 (-)

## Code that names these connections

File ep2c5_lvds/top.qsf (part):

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set_location_assignment PIN_A5 -to ft_data[10]
set_location_assignment PIN_B4 -to ft_data[9]
set_location_assignment PIN_A4 -to ft_data[8]
set_location_assignment PIN_B3 -to ft_clk
set_location_assignment PIN_A3 -to ft_data[7]
set_location_assignment PIN_C2 -to ft_data[6]
set_location_assignment PIN_C1 -to ft_data[5]
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set_location_assignment PIN_F2 -to ft_data[0]
set_location_assignment PIN_A8 -to ft_be[0]
set_location_assignment PIN_B8 -to ft_be[1]
set_location_assignment PIN_A9 -to ft_txe_n
set_location_assignment PIN_B9 -to ft_rxf_n
set_location_assignment PIN_B10 -to ft_rd_n
set_location_assignment PIN_A11 -to ft_oe_n
set_location_assignment PIN_B11 -to ft_reset_n
set_location_assignment PIN_A10 -to ft_wr_n
set_location_assignment PIN_C9 -to ft_gpio[0]
set_location_assignment PIN_D9 -to ft_gpio[1]
set_location_assignment PIN_D11 -to ft_wakeup_n
set_global_assignment -name USE_CONFIGURATION_DEVICE ON
set_global_assignment -name CRC_ERROR_CHECKING ON
set_global_assignment -name RESERVE_ALL_UNUSED_PINS "AS INPUT TRI-STATED WITH WEAK PULL-UP"
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set_location_assignment PIN_J22 -to dig_input[2]
set_location_assignment PIN_K21 -to dig_input[1]
set_location_assignment PIN_K22 -to dig_input[0]
set_location_assignment PIN_L22 -to dig_clk
set_instance_assignment -name PARTITION_HIERARCHY root_partition -to | -section_id Top
set_location_assignment PIN_G1 -to led[0]
set_location_assignment PIN_G2 -to led[1]
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
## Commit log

2023-02-10 Front-end schematic.
2023-02-13 Probe schematic.
2023-02-13 Ignore backups.
2023-02-13 Rev 1. Before using HP pod.
2023-02-13 Various docs.
2023-02-13 Update front-end with new values.
2023-02-14 Front-end placement exercise.
2023-02-16 EP2C5 LVDS. EP2C35 symbol (WIP)
2023-02-21 ep2c35 trial. WIP.
2023-02-27 Wire up FTDI FT600Q.
2023-02-27 Before switching to hierarchical sheets.
2023-02-27 Fix tons of ERC violations.
2023-03-02 Power supplies.
2023-03-05 Add digital interface. Power islands.
2023-03-05 Create assembly file. WIP.
2023-03-06 Move JLCPCB components to bottom.
2023-03-07 Add lvds_tx.
2023-03-13 Top ground plan.
2023-03-13 Add ESD protection.
2023-03-13 Add LM317A power regulators.
2023-03-24 Add schematic of a few logic analyzers.
2023-03-24 Rename la mapping.
2024-03-07 Update README.
2024-03-07 EP2C5 experiment.
2024-03-07 la_digital
2024-03-07 Unknown logic_analyzer changes.
2024-03-07 Saleae.
2024-03-07 Missing file.
2024-03-07 hp16550a. Unknown changes.
2024-03-07 ep2c35_trail. Unknown changes.
2025-03-24 Make symbol paths relative to project.
2025-03-24 Rename EP2C5 to EP2C35.

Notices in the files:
ep2c5_lvds/top.qsf:
Copyright (C) 1991-2013 Altera Corporation
